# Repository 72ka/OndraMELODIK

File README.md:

# OndraMELODIK

 Music interface for the famous czechoslovak home computer [TESLA Ondra SPO186](http://www.ondraspo186.8u.cz/ "Tento web se zabývá československým počítačem Tesla Ondra SPO 186")

 SMD version with Joystick interface, but without printer connector by Solaris104 here: [Ondra JOY/MELODIK](http://www.ondraspo186.8u.cz/?p=641).
 
 You can read the OndraMELODIK story in [this article](http://www.ondraspo186.8u.cz/?p=588) (Czech language)

> OndraMELODIK music interface - introduced in 2022

> Czechoslovak home computer Tesla Ondra SPO186 - introduced in 1985

### Features

- Opensource hardware
- Based on [SN76489](https://en.wikipedia.org/wiki/Texas_Instruments_SN76489) chip
- Compatible with [OndraSD](https://sites.google.com/site/ondraspo186/4-rom-card-sd) interface, OndraMELODIK is through out interface
- It can play 3 channels square wave, 1 channel noise simultaneously
- Minimum CPU usage - two byte transfer, in some cases even one byte transfer, this is essential for such a slow computer
- External interface - no changes on the computer
- Designed with 80´ technology - all parts was available in 1985
- DB25 Centronics printer port (formerly known as LPT from PC) in one case
- 3D printed case STL files included

### Usage

1. Turn off your belowed Ondra
2. Plug OndraMELODIK to Ondra X1 connector
3. Optionally plug the OndraSD or whatever interface to the OndraMELODIK

#### As music interface

4. Switch the switch to the MELODIK position
5. Plug the 3.5mm audio jack of your favorite audio system
6. Turn on Ondra
7. If you hear some noise or tone, just push once the RESET button
8. Load the software [meltest.bin](https://github.com/72ka/OndraMELODIK/raw/main/Software/demo_test.bin) from this repository and test the device and listen the music

> Notice: If you perform just Ondra reset and some tone or noise is coming out, just push the RESET button once

#### As printer interface

4. Switch the switch to the PRINTER position
5. Be sure you dont have plugged in the audio jack or the audio system is turned off
6. Plug your printer using standard PC printer cable
7. Turn on Ondra
8. Print using Ondra's monitor, BASIC or TEDIT (if you forget to unplug the audio jack and strange noises are coming out, it is normal)

### Preview

How it sounds

https://www.youtube.com/watch?v=u5RyUs0VGdg

How it prints

https://www.youtube.com/watch?v=VYsxnQOKPeM

### Real photos

### License

MIT license

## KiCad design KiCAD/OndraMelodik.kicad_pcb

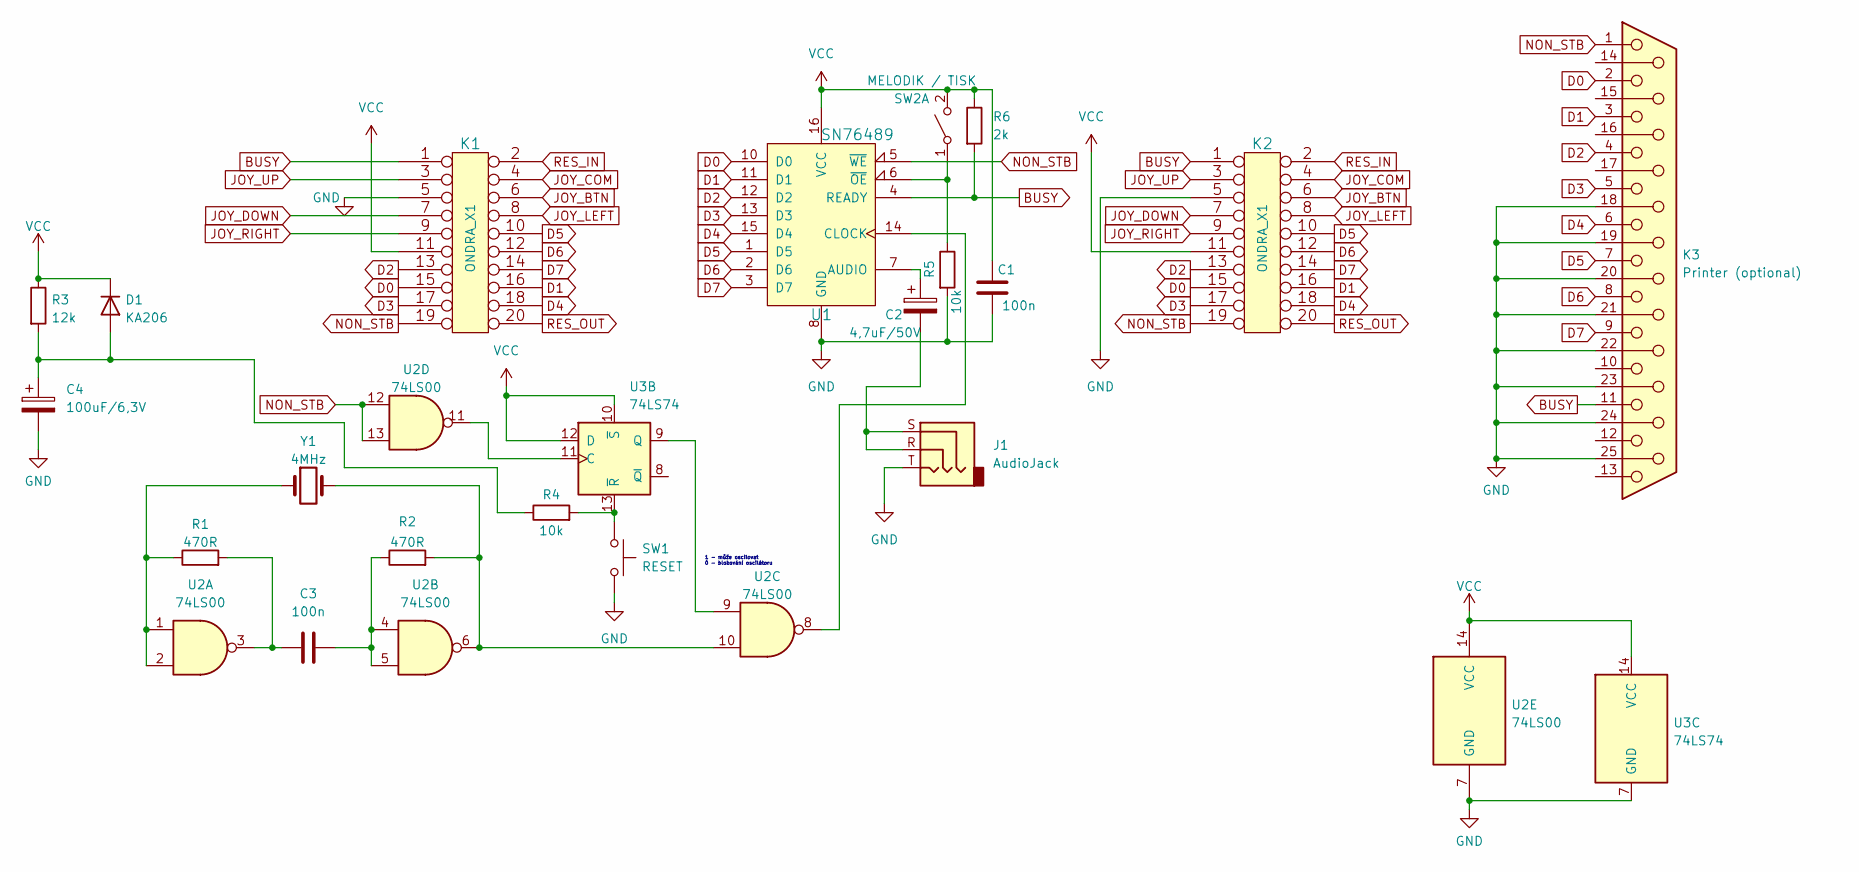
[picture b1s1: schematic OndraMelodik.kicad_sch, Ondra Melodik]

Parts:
C1, C3: 100n; C_Disc_D3.0mm_W1.6mm_P2.50mm
C2: 4,7uF/50V; C_Radial_D5.0mm_H7.0mm_P2.00mm
C4: 100uF/6,3V; C_Radial_D6.3mm_H7.0mm_P2.50mm
D1: KA206; D_A-405_P7.62mm_Horizontal
J1: AudioJack; Jack_3.5mm_Lumberg_1503_07_Horizontal
K1, K2: ONDRA_X1; TX5112011
K3: Printer (optional); DSUB-25_Female_EdgeMount_P2.77mm
R1, R2: 470R; R_Axial_DIN0207_L6.3mm_D2.5mm_P7.62mm_Horizontal
R3: 12k; R_Axial_DIN0207_L6.3mm_D2.5mm_P7.62mm_Horizontal
R4, R5: 10k; R_Axial_DIN0207_L6.3mm_D2.5mm_P7.62mm_Horizontal
R6: 2k; R_Axial_DIN0207_L6.3mm_D2.5mm_P7.62mm_Horizontal
SW1: RESET; SW_PUSH_6mm
SW2: MELODIK / TISK; SW_CuK_JS202011CQN_DPDT_Straight
U1: SN76489; DIP-16_W7.62mm
U2: 74LS00; DIP-14_W7.62mm
U3: 74LS74; DIP-14_W7.62mm
Y1: 4MHz; Crystal_HC49-4H_Vertical

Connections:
BUSY: K1.1, K2.1, K3.11, R6.2, U1.4 (READY)
D0: K1.15, K2.15, K3.2, U1.10 (D0)
D1: K1.16, K2.16, K3.3, U1.11 (D1)
D2: K1.13, K2.13, K3.4, U1.12 (D2)
D3: K1.17, K2.17, K3.5, U1.13 (D3)
D4: K1.18, K2.18, K3.6, U1.15 (D4)
D5: K1.10, K2.10, K3.7, U1.1 (D5)
D6: K1.12, K2.12, K3.8, U1.2 (D6)
D7: K1.14, K2.14, K3.9, U1.3 (D7)
GND: C1.2, C4.2, J1.T, K1.5, K2.5, K3.18, K3.19, K3.20, K3.21, K3.22, K3.23, K3.24, K3.25, R5.2, SW1.2, U1.8 (GND), U2.7 (GND), U3.7 (GND)
JOY_BTN: K1.6, K2.6
JOY_COM: K1.4, K2.4
JOY_DOWN: K1.7, K2.7
JOY_LEFT: K1.8, K2.8
JOY_RIGHT: K1.9, K2.9
JOY_UP: K1.3, K2.3
NON_STB: K1.19, K2.19, K3.1, U1.5 (~WE), U2.12, U2.13
unnamed: C2.1, U1.7 (AUDIO)
unnamed: C2.2, J1.R, J1.S
unnamed: C3.1, R1.2, U2.3
unnamed: C3.2, R2.1, U2.4, U2.5
unnamed: C4.1, D1.2 (A), R3.2, R4.1
unnamed: R1.1, U2.1, U2.2, Y1.1
unnamed: R2.2, U2.6, U2.10, Y1.2
unnamed: R4.2, SW1.1, U3.13 (~R)
unnamed: R5.1, SW2.1 (A), U1.6 (~OE)
unnamed: U1.14 (CLOCK), U2.8
unnamed: U2.9, U3.9 (Q)
unnamed: U2.11, U3.11 (C)
RES_IN: K1.2, K2.2
RES_OUT: K1.20, K2.20
VCC: C1.1, D1.1 (K), K1.11, K2.11, R3.1, R6.1, SW2.2 (B), U1.16 (VCC), U2.14 (VCC), U3.10 (~S), U3.12 (D), U3.14 (VCC)

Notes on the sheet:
1 - může oscilovat 0 - blokování oscilátoru

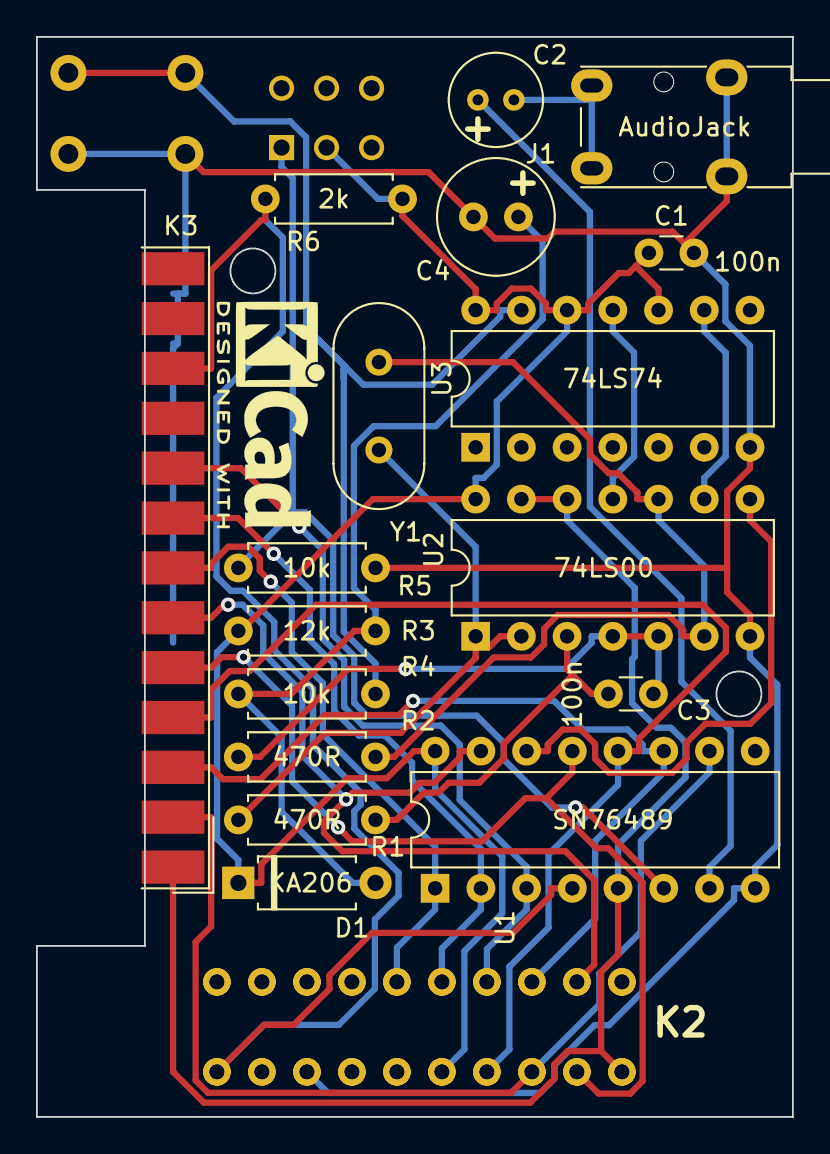
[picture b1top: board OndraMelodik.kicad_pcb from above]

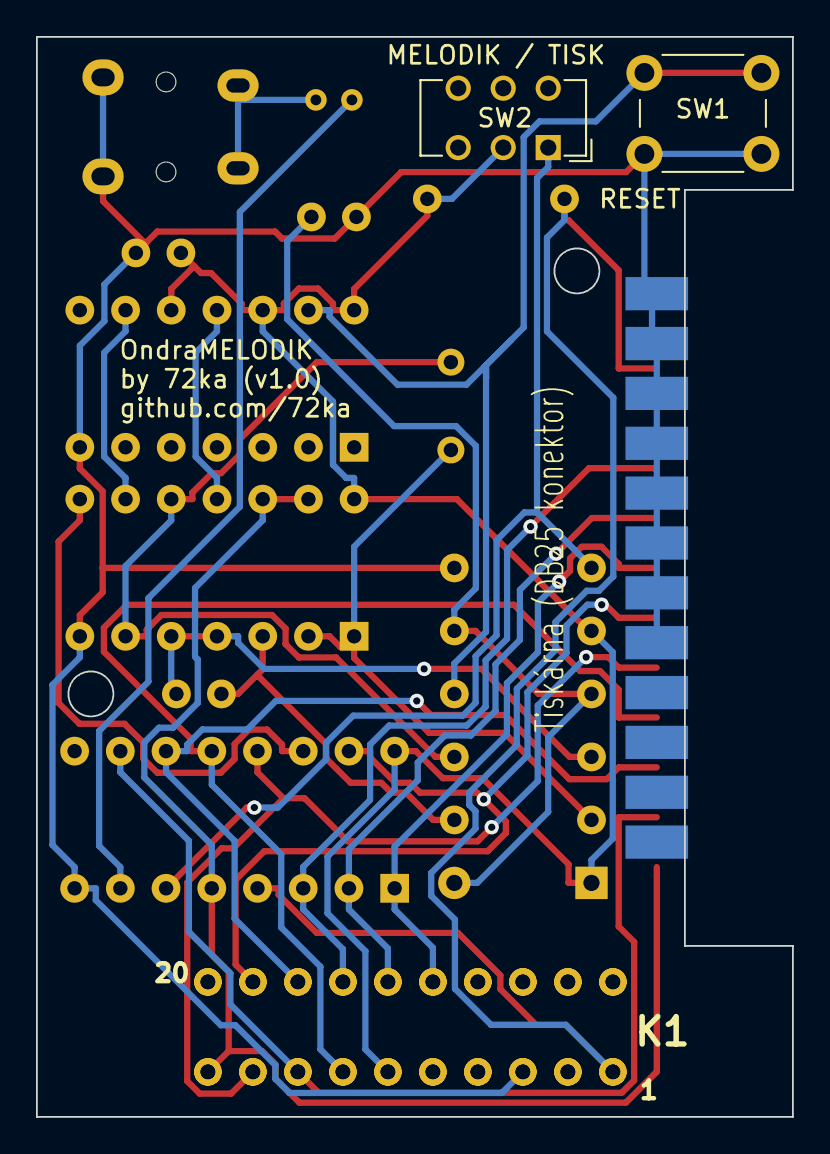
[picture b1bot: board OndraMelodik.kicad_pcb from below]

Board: 2 copper layers, 42.0 x 60.0 mm, 21 parts (2 on the bottom side), 32 nets.

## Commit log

2022-08-25 Add files via upload
    real photos
2023-04-16 Pridana informace o clanku
2023-04-19 Create FallingBlocks.bin
    Added the Falling Blocks v2 game with fixed bugs (realy and melodik detection)
2023-04-19 Update FallingBlocks.bin
    Named as v2b
2023-04-19 Update FallingBlocks.bin
    Bug fixes
2023-04-23 Basic set of Z80 asm routines
    This is the essential set of the assembler routines to control OndraMELODIK on the Ondra computer used in my software.
    They are well commented, feel free to use.
2023-04-23 Clean code
2026-02-10 Update README.md
    Added link to Solaris104 SMD version of this module
